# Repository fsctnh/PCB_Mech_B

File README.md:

# Keypad Mecânico
Minha primeira PCB de teclado, Compatível com switches MX-Alps Hybrid, não é hotswap
Usando Atmega32u4

Special Thanks: Ai03

## Top View:

## Bottom view:

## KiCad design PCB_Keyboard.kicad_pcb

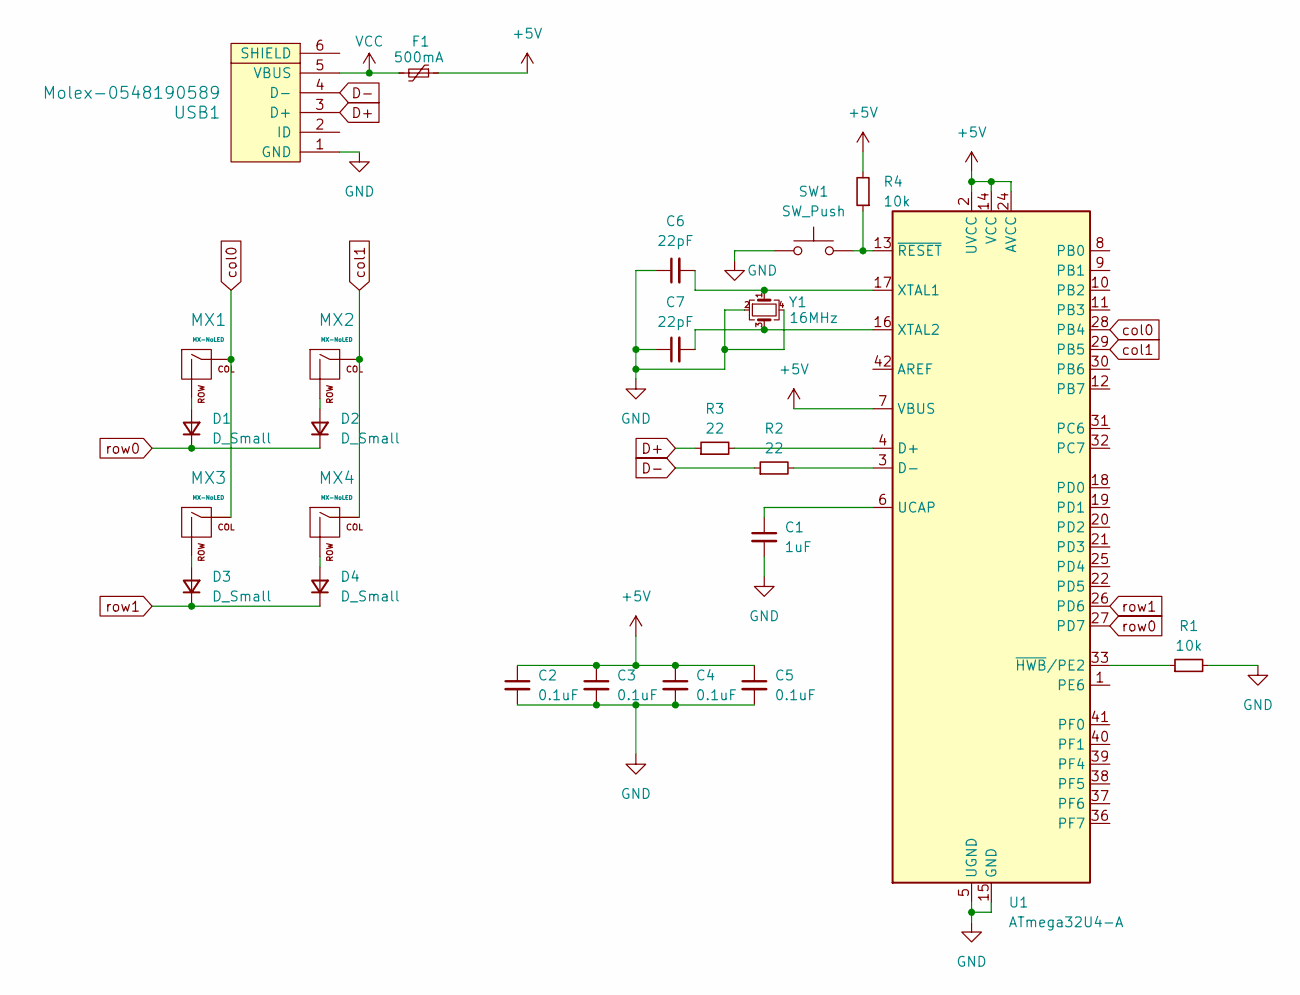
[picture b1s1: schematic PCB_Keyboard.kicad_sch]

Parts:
C1: 1uF; C_0805_2012Metric
C2, C3, C4, C5: 0.1uF; C_0805_2012Metric
C6, C7: 22pF; C_0805_2012Metric
D1, D2, D3, D4: D_Small; D_SOD-123
F1: 500mA; Fuse_1206_3216Metric
MX1, MX2, MX3, MX4: MX-NoLED; MX-Alps-Hybrid-1U
R1, R4: 10k; R_0805_2012Metric
R2, R3: 22; R_0805_2012Metric
SW1: SW_Push; SKQG-1155865
U1: ATmega32U4-A; TQFP-44_10x10mm_P0.8mm
USB1: Molex-0548190589
Y1: 16MHz; Crystal_SMD_3225-4Pin_3.2x2.5mm

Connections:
+5V: C2.1, C3.1, C4.1, C5.1, F1.1, R4.2, U1.2 (UVCC), U1.7 (VBUS), U1.14 (VCC), U1.24 (AVCC), U1.34 (VCC), U1.44 (AVCC)
D+: R3.1, USB1.3 (D+)
D-: R2.1, USB1.4 (D-)
GND: C1.2, C2.2, C3.2, C4.2, C5.2, C6.1, C7.1, R1.2, SW1.1, U1.5 (UGND), U1.15 (GND), U1.23 (GND), U1.35 (GND), U1.43 (GND), USB1.1 (GND), Y1.2, Y1.4
unnamed: D1.2 (A), MX1.2 (ROW)
unnamed: D2.2 (A), MX2.2 (ROW)
unnamed: D3.2 (A), MX3.2 (ROW)
unnamed: D4.2 (A), MX4.2 (ROW)
unnamed: R3.2, U1.4 (D+)
unnamed: R2.2, U1.3 (D-)
unnamed: C1.1, U1.6 (UCAP)
unnamed: C6.2, U1.17 (XTAL1), Y1.1
unnamed: C7.2, U1.16 (XTAL2), Y1.3
unnamed: R1.1, U1.33 (~HWB/PE2)
unnamed: R4.1, SW1.2, U1.13 (~RESET)
VCC: F1.2, USB1.5 (VBUS)
col0: MX1.1 (COL), MX3.1 (COL), U1.28 (PB4)
col1: MX2.1 (COL), MX4.1 (COL), U1.29 (PB5)
row0: D1.1 (K), D2.1 (K), U1.27 (PD7)
row1: D3.1 (K), D4.1 (K), U1.26 (PD6)

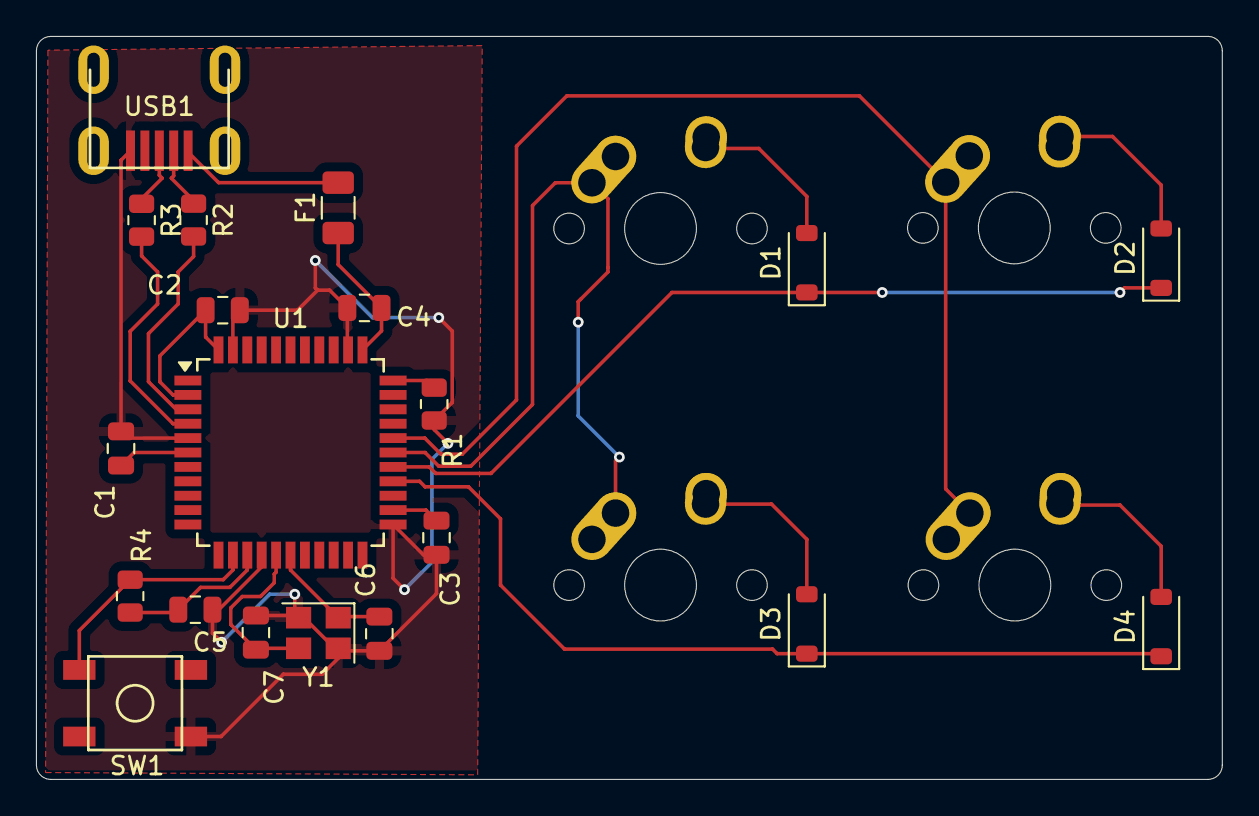
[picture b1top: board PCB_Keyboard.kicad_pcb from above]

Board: 2 copper layers, 65.9 x 41.3 mm, 24 parts (0 on the bottom side), 20 nets.
